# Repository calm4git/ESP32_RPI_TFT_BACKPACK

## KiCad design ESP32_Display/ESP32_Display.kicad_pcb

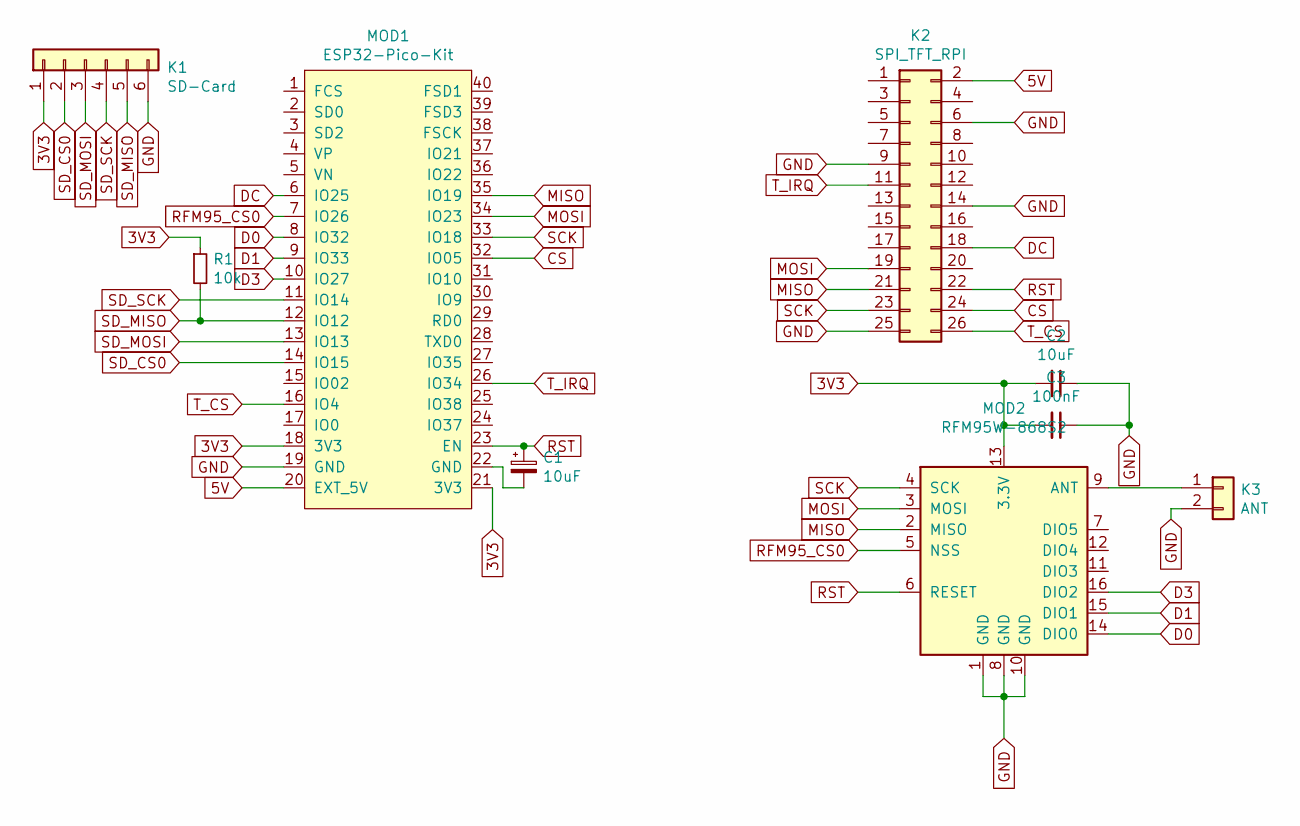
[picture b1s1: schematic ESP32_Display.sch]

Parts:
C1, C2: 10uF; C_0805_2012Metric_Pad1.15x1.40mm_HandSolder
C3: 100nF; C_0805_2012Metric_Pad1.15x1.40mm_HandSolder
K1: SD-Card; PinSocket_1x06_P2.54mm_Vertical
K2: SPI_TFT_RPI; PinHeader_2x13_P2.54mm_Vertical
K3: ANT; PinHeader_1x02_P2.54mm_Vertical
MOD1: ESP32-Pico-Kit; DIP-40_W15.24mm_Socket
MOD2: RFM95W-868S2; HOPERF_RFM9XW_SMD
R1: 10k; R_0805_2012Metric_Pad1.15x1.40mm_HandSolder

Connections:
3V3: C2.2, C3.2, K1.1, MOD1.18 (3V3), MOD1.21 (3V3), MOD2.13 (3.3V), R1.1
5V: K2.2, MOD1.20 (EXT_5V)
CS: K2.24, MOD1.32 (IO05)
D0: MOD1.8 (IO32), MOD2.14 (DIO0)
D1: MOD1.9 (IO33), MOD2.15 (DIO1)
D3: MOD1.10 (IO27), MOD2.16 (DIO2)
DC: K2.18, MOD1.6 (IO25)
GND: C2.1, C3.1, K1.6, K2.6, K2.9, K2.14, K2.25, K3.2, MOD1.19 (GND), MOD2.1 (GND), MOD2.8 (GND), MOD2.10 (GND)
MISO: K2.21, MOD1.35 (IO19), MOD2.2 (MISO)
MOSI: K2.19, MOD1.34 (IO23), MOD2.3 (MOSI)
unnamed: C1.2, MOD1.22 (GND)
unnamed: K3.1, MOD2.9 (ANT)
RFM95_CS0: MOD1.7 (IO26), MOD2.5 (NSS)
RST: C1.1, K2.22, MOD1.23 (EN), MOD2.6 (RESET)
SCK: K2.23, MOD1.33 (IO18), MOD2.4 (SCK)
SD_CS0: K1.2, MOD1.14 (IO15)
SD_MISO: K1.5, MOD1.12 (IO12), R1.2
SD_MOSI: K1.3, MOD1.13 (IO13)
SD_SCK: K1.4, MOD1.11 (IO14)
T_CS: K2.26, MOD1.16 (IO4)
T_IRQ: K2.11, MOD1.26 (IO34)

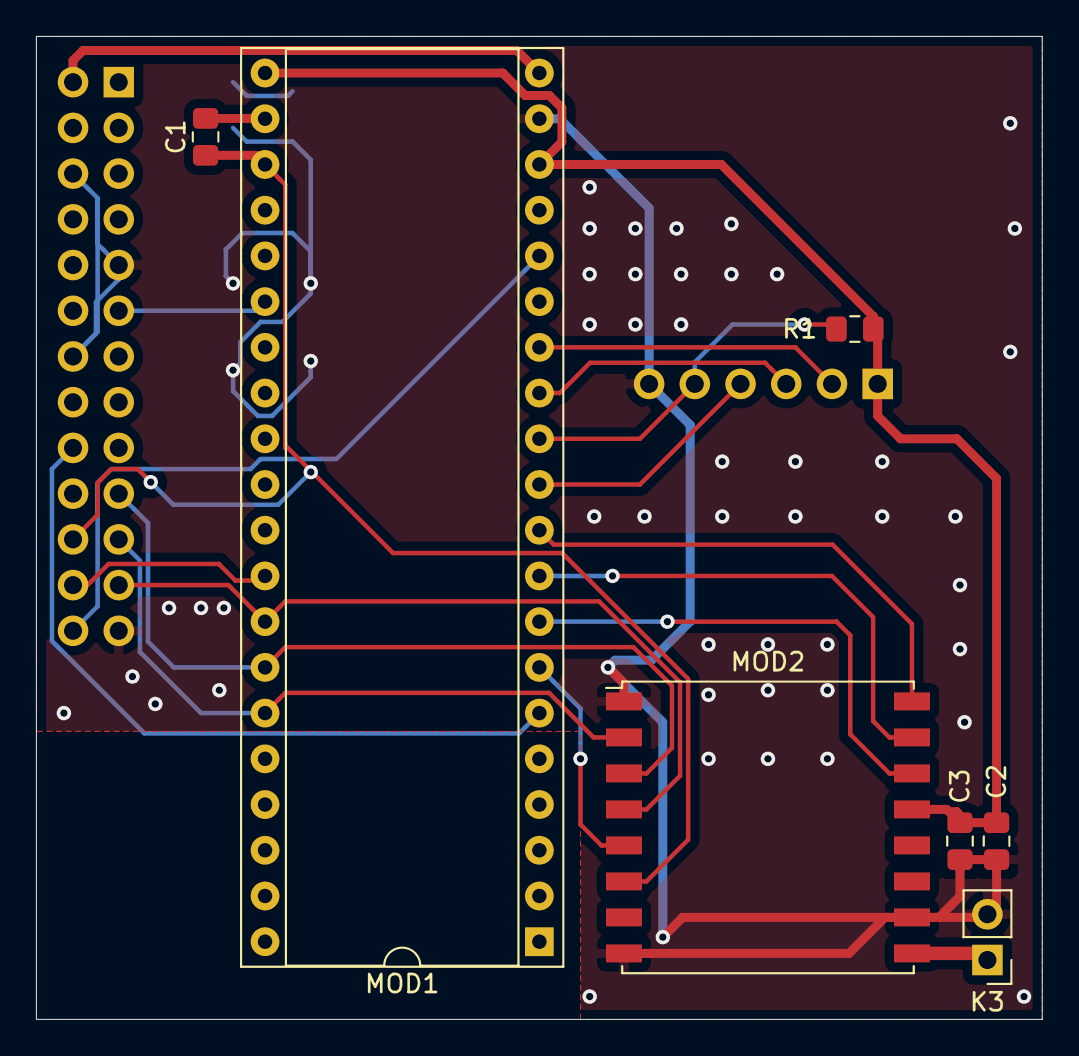
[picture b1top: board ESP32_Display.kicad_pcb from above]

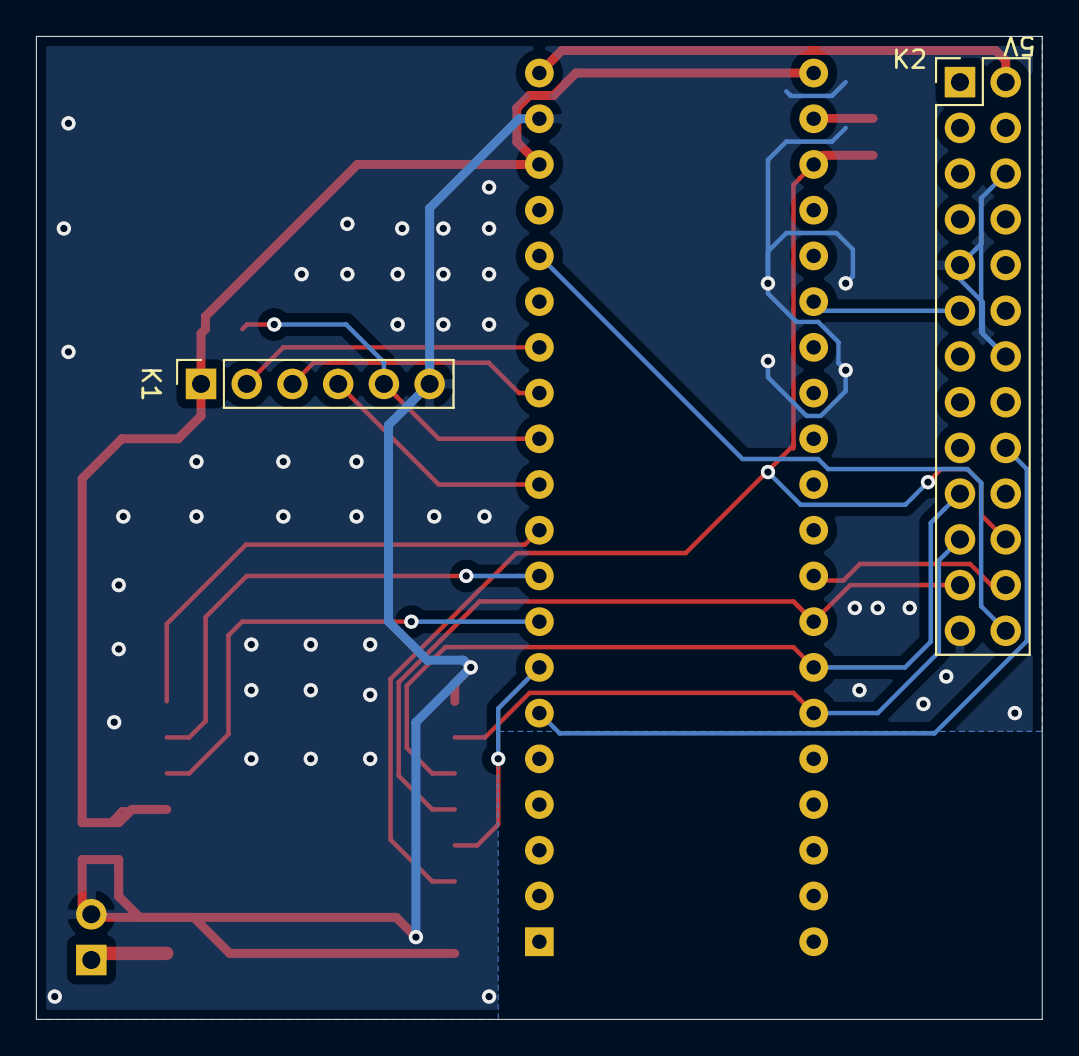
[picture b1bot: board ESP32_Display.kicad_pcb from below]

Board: 2 copper layers, 55.9 x 54.6 mm, 9 parts (2 on the bottom side), 21 nets.
